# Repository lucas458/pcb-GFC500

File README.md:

# pcb-GFC500
Placa do Garmin GFC-500

### GFC-500 Real

### Placa Frontal

### Interface USB

### Placa Frontal e Interface USB

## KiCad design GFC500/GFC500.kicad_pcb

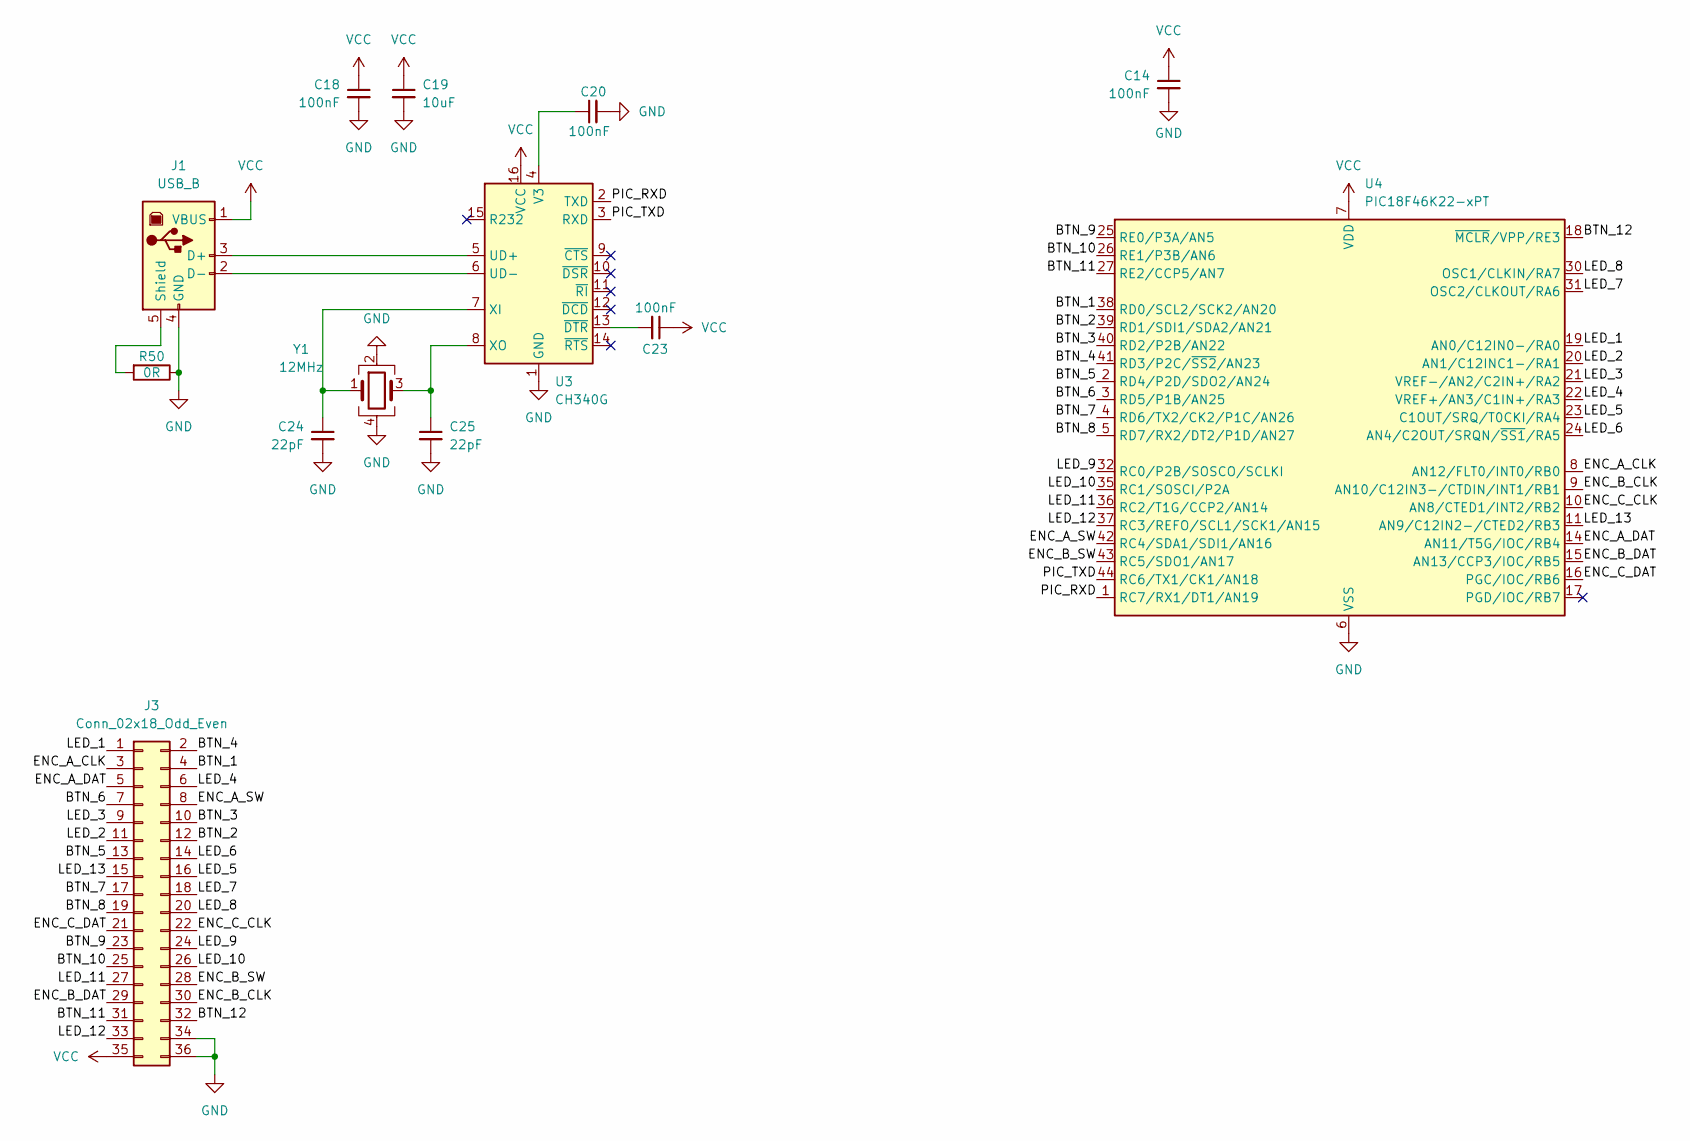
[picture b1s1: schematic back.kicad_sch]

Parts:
C14, C18, C20, C23: 100nF; C_0603_1608Metric
C19: 10uF; C_0805_2012Metric
C24, C25: 22pF; C_0603_1608Metric
J1: USB_B; A-USBSB
J3: Conn_02x18_Odd_Even; CONN36_901303436_MOL_H
R50: 0R; R_0603_1608Metric
U3: CH340G; SOIC-16_3.9x9.9mm_P1.27mm
U4: PIC18F46K22-xPT; TQFP-44_10x10mm_P0.8mm
Y1: 12MHz; Crystal_SMD_3225-4Pin_3.2x2.5mm

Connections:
/Back/BTN_1: J3.4, U4.38 (RD0/SCL2/SCK2/AN20)
/Back/BTN_2: J3.12, U4.39 (RD1/SDI1/SDA2/AN21)
/Back/BTN_3: J3.10, U4.40 (RD2/P2B/AN22)
/Back/BTN_4: J3.2, U4.41 (RD3/P2C/~SS2/AN23)
/Back/BTN_5: J3.13, U4.2 (RD4/P2D/SDO2/AN24)
/Back/BTN_6: J3.7, U4.3 (RD5/P1B/AN25)
/Back/BTN_7: J3.17, U4.4 (RD6/TX2/CK2/P1C/AN26)
/Back/BTN_8: J3.19, U4.5 (RD7/RX2/DT2/P1D/AN27)
/Back/BTN_9: J3.23, U4.25 (RE0/P3A/AN5)
/Back/BTN_10: J3.25, U4.26 (RE1/P3B/AN6)
/Back/BTN_11: J3.31, U4.27 (RE2/CCP5/AN7)
/Back/BTN_12: J3.32, U4.18 (~MCLR/VPP/RE3)
/Back/ENC_A_CLK: J3.3, U4.8 (AN12/FLT0/INT0/RB0)
/Back/ENC_A_DAT: J3.5, U4.14 (AN11/T5G/IOC/RB4)
/Back/ENC_A_SW: J3.8, U4.42 (RC4/SDA1/SDI1/AN16)
/Back/ENC_B_CLK: J3.30, U4.9 (AN10/C12IN3-/CTDIN/INT1/RB1)
/Back/ENC_B_DAT: J3.29, U4.15 (AN13/CCP3/IOC/RB5)
/Back/ENC_B_SW: J3.28, U4.43 (RC5/SDO1/AN17)
/Back/ENC_C_CLK: J3.22, U4.10 (AN8/CTED1/INT2/RB2)
/Back/ENC_C_DAT: J3.21, U4.16 (PGC/IOC/RB6)
/Back/LED_1: J3.1, U4.19 (AN0/C12IN0-/RA0)
/Back/LED_2: J3.11, U4.20 (AN1/C12INC1-/RA1)
/Back/LED_3: J3.9, U4.21 (VREF-/AN2/C2IN+/RA2)
/Back/LED_4: J3.6, U4.22 (VREF+/AN3/C1IN+/RA3)
/Back/LED_5: J3.16, U4.23 (C1OUT/SRQ/T0CKI/RA4)
/Back/LED_6: J3.14, U4.24 (AN4/C2OUT/SRQN/~SS1/RA5)
/Back/LED_7: J3.18, U4.31 (OSC2/CLKOUT/RA6)
/Back/LED_8: J3.20, U4.30 (OSC1/CLKIN/RA7)
/Back/LED_9: J3.24, U4.32 (RC0/P2B/SOSCO/SCLKI)
/Back/LED_10: J3.26, U4.35 (RC1/SOSCI/P2A)
/Back/LED_11: J3.27, U4.36 (RC2/T1G/CCP2/AN14)
/Back/LED_12: J3.33, U4.37 (RC3/REFO/SCL1/SCK1/AN15)
/Back/LED_13: J3.15, U4.11 (AN9/C12IN2-/CTED2/RB3)
/Back/PIC_RXD: U3.2 (TXD), U4.1 (RC7/RX1/DT1/AN19)
/Back/PIC_TXD: U3.3 (RXD), U4.44 (RC6/TX1/CK1/AN18)
GND: C14.2, C18.2, C19.2, C20.2, C24.2, C25.2, J1.4 (GND), J3.34, J3.36, R50.1, U3.1 (GND), U4.6 (VSS), U4.29 (VSS), Y1.2, Y1.4; also elsewhere on the board
unnamed: J1.3 (D+), U3.5 (UD+)
unnamed: J1.2 (D-), U3.6 (UD-)
unnamed: J1.5 (Shield), R50.2
unnamed: C20.1, U3.4 (V3)
unnamed: C24.1, U3.7 (XI), Y1.1
unnamed: C25.1, U3.8 (XO), Y1.3
unnamed: C23.2, U3.13 (~DTR)
VCC: C14.1, C18.1, C19.1, C23.1, J1.1 (VBUS), J3.35, U3.16 (VCC), U4.7 (VDD), U4.28 (VDD); also elsewhere on the board

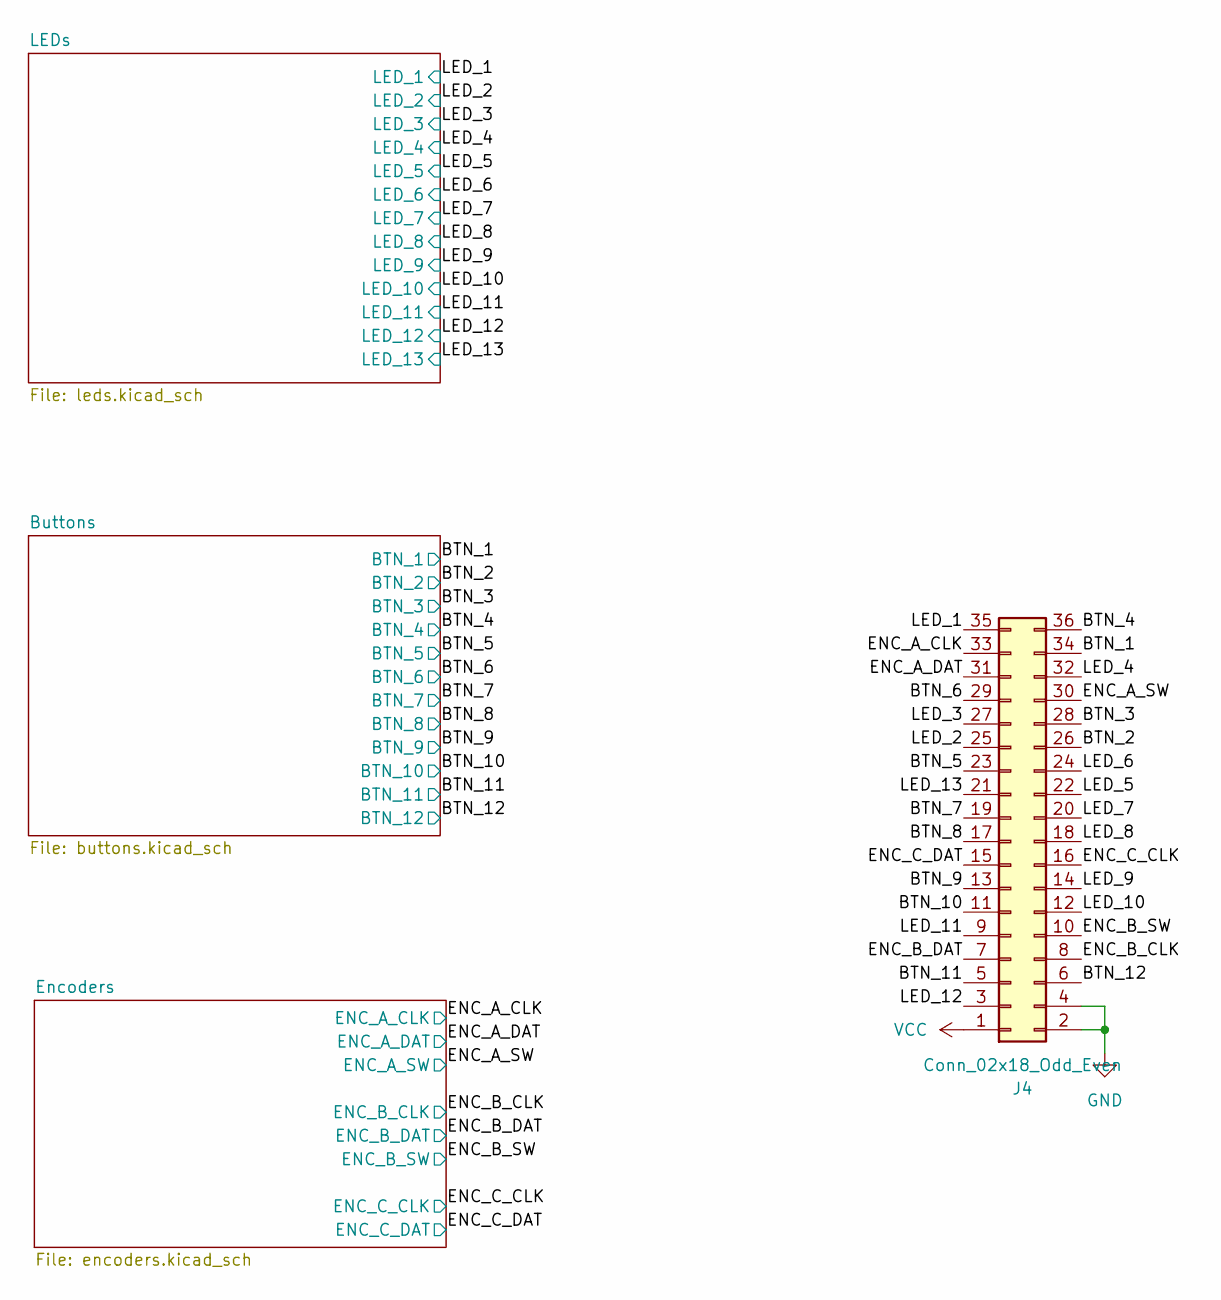
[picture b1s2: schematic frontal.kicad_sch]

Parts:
J4: Conn_02x18_Odd_Even; CONN36_901301436_MOL

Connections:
/Frontal/BTN_1: J4.34; also elsewhere on the board
/Frontal/BTN_2: J4.26; also elsewhere on the board
/Frontal/BTN_3: J4.28; also elsewhere on the board
/Frontal/BTN_4: J4.36; also elsewhere on the board
/Frontal/BTN_5: J4.23; also elsewhere on the board
/Frontal/BTN_6: J4.29; also elsewhere on the board
/Frontal/BTN_7: J4.19; also elsewhere on the board
/Frontal/BTN_8: J4.17; also elsewhere on the board
/Frontal/BTN_9: J4.13; also elsewhere on the board
/Frontal/BTN_10: J4.11; also elsewhere on the board
/Frontal/BTN_11: J4.5; also elsewhere on the board
/Frontal/BTN_12: J4.6; also elsewhere on the board
/Frontal/ENC_A_CLK: J4.33; also elsewhere on the board
/Frontal/ENC_A_DAT: J4.31; also elsewhere on the board
/Frontal/ENC_A_SW: J4.30; also elsewhere on the board
/Frontal/ENC_B_CLK: J4.8; also elsewhere on the board
/Frontal/ENC_B_DAT: J4.7; also elsewhere on the board
/Frontal/ENC_B_SW: J4.10; also elsewhere on the board
/Frontal/ENC_C_CLK: J4.16; also elsewhere on the board
/Frontal/ENC_C_DAT: J4.15; also elsewhere on the board
/Frontal/LED_1: J4.35; also elsewhere on the board
/Frontal/LED_2: J4.25; also elsewhere on the board
/Frontal/LED_3: J4.27; also elsewhere on the board
/Frontal/LED_4: J4.32; also elsewhere on the board
/Frontal/LED_5: J4.22; also elsewhere on the board
/Frontal/LED_6: J4.24; also elsewhere on the board
/Frontal/LED_7: J4.20; also elsewhere on the board
/Frontal/LED_8: J4.18; also elsewhere on the board
/Frontal/LED_9: J4.14; also elsewhere on the board
/Frontal/LED_10: J4.12; also elsewhere on the board
/Frontal/LED_11: J4.9; also elsewhere on the board
/Frontal/LED_12: J4.3; also elsewhere on the board
/Frontal/LED_13: J4.21; also elsewhere on the board
GND: J4.2, J4.4; also elsewhere on the board
VCC: J4.1; also elsewhere on the board

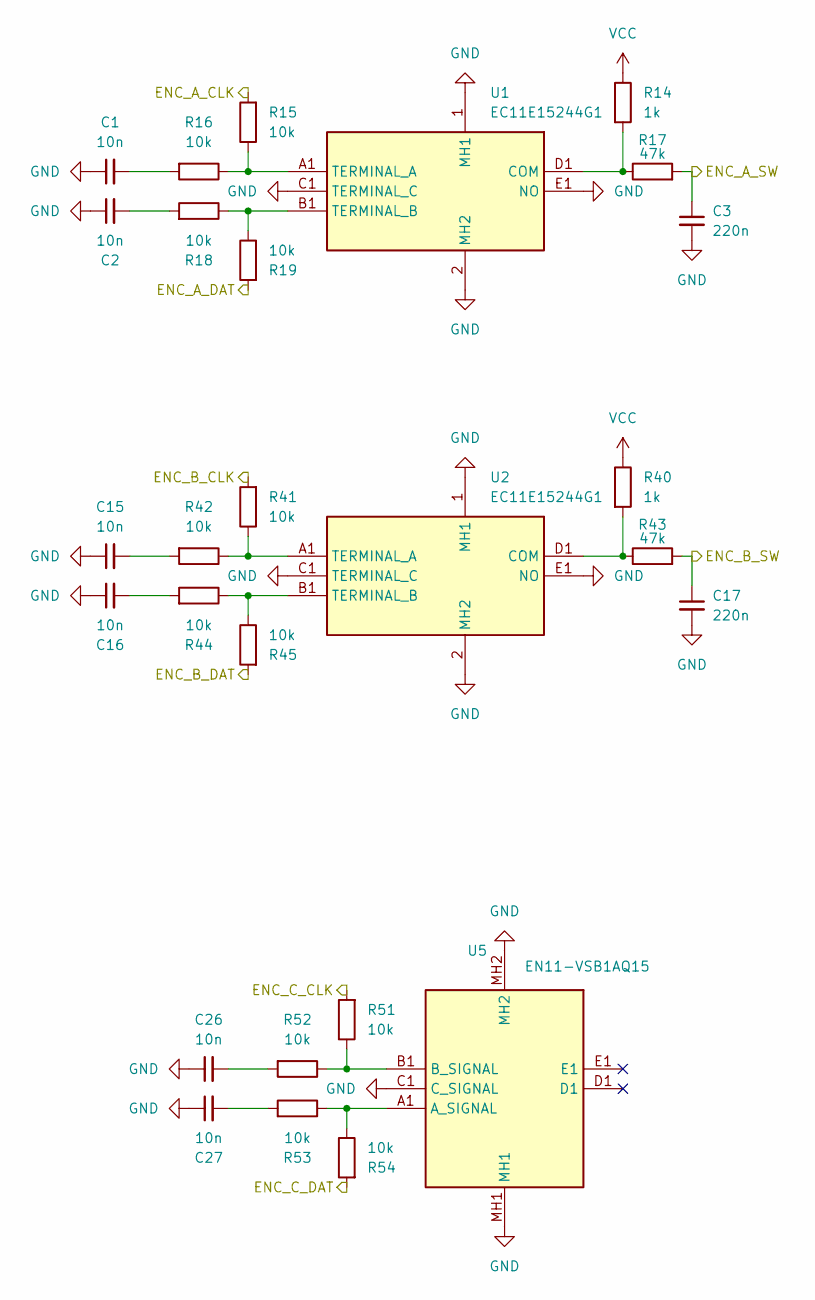
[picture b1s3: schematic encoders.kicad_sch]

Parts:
C1, C2, C15, C16, C26, C27: 10n; C_0603_1608Metric
C3, C17: 220n; C_0603_1608Metric
R14, R40: 1k; R_0603_1608Metric
R15, R16, R18, R19, R41, R42, R44, R45, R51, R52, R53, R54: 10k; R_0603_1608Metric
R17, R43: 47k; R_0603_1608Metric
U1, U2: EC11E15244G1; Manufacturer_Part_Number EC11E15244G1; Mouser Part Number 688-EC11E15244G1
U5: EN11-VSB1AQ15; EN11VSB1AQ15; Manufacturer_Part_Number EN11-VSB1AQ15; Mouser Part Number 858-EN11-VSB1AQ15

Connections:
/Frontal/ENC_A_CLK: R15.2; also elsewhere on the board
/Frontal/ENC_A_DAT: R19.2; also elsewhere on the board
/Frontal/ENC_A_SW: C3.1, R17.2; also elsewhere on the board
/Frontal/ENC_B_CLK: R41.2; also elsewhere on the board
/Frontal/ENC_B_DAT: R45.2; also elsewhere on the board
/Frontal/ENC_B_SW: C17.1, R43.2; also elsewhere on the board
/Frontal/ENC_C_CLK: R51.2; also elsewhere on the board
/Frontal/ENC_C_DAT: R54.2; also elsewhere on the board
GND: C1.1, C2.1, C3.2, C15.1, C16.1, C17.2, C26.1, C27.1, U1.1 (MH1), U1.2 (MH2), U1.C1 (TERMINAL_C), U1.E1 (NO), U2.1 (MH1), U2.2 (MH2), U2.C1 (TERMINAL_C), U2.E1 (NO), U5.C1 (C_SIGNAL), U5.MH1, U5.MH2; also elsewhere on the board
unnamed: C1.2, R16.2
unnamed: C2.2, R18.2
unnamed: C15.2, R42.2
unnamed: C16.2, R44.2
unnamed: C26.2, R52.2
unnamed: C27.2, R53.2
unnamed: R14.2, R17.1, U1.D1 (COM)
unnamed: R15.1, R16.1, U1.A1 (TERMINAL_A)
unnamed: R18.1, R19.1, U1.B1 (TERMINAL_B)
unnamed: R40.2, R43.1, U2.D1 (COM)
unnamed: R41.1, R42.1, U2.A1 (TERMINAL_A)
unnamed: R44.1, R45.1, U2.B1 (TERMINAL_B)
unnamed: R53.1, R54.1, U5.A1 (A_SIGNAL)
unnamed: R51.1, R52.1, U5.B1 (B_SIGNAL)
VCC: R14.1, R40.1; also elsewhere on the board

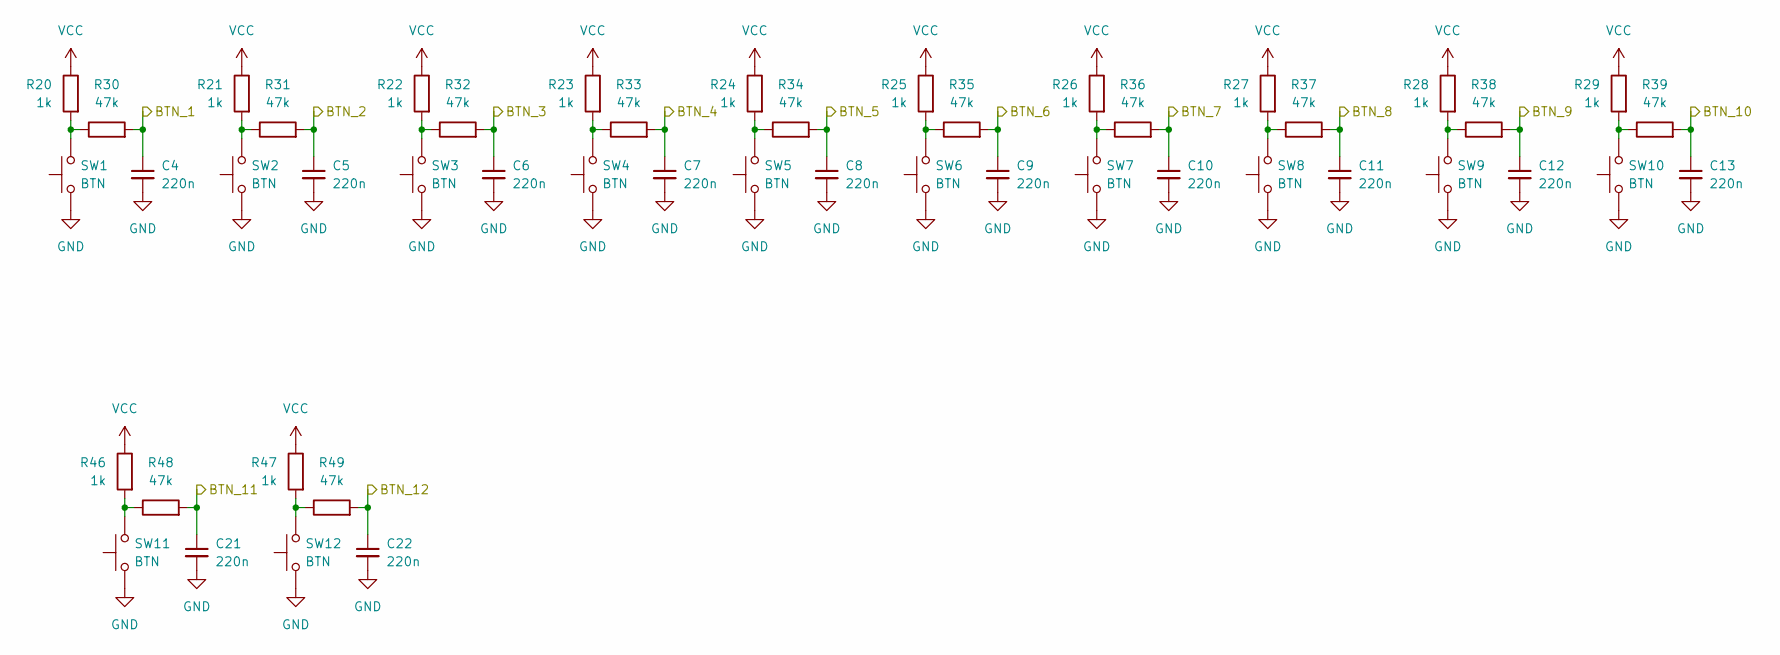
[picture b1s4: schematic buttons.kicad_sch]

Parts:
C4, C5, C6, C7, C8, C9, C10, C11, C12, C13, C21, C22: 220n; C_0603_1608Metric
R20, R21, R22, R23, R24, R25, R26, R27, R28, R29, R46, R47: 1k; R_0603_1608Metric
R30, R31, R32, R33, R34, R35, R36, R37, R38, R39, R48, R49: 47k; R_0603_1608Metric
SW1, SW2, SW3, SW4, SW5, SW6, SW7, SW8, SW9, SW10, SW11, SW12: BTN; SW_SPST_PTS647_Sx50

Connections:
/Frontal/BTN_1: C4.1, R30.2; also elsewhere on the board
/Frontal/BTN_2: C5.1, R31.2; also elsewhere on the board
/Frontal/BTN_3: C6.1, R32.2; also elsewhere on the board
/Frontal/BTN_4: C7.1, R33.2; also elsewhere on the board
/Frontal/BTN_5: C8.1, R34.2; also elsewhere on the board
/Frontal/BTN_6: C9.1, R35.2; also elsewhere on the board
/Frontal/BTN_7: C10.1, R36.2; also elsewhere on the board
/Frontal/BTN_8: C11.1, R37.2; also elsewhere on the board
/Frontal/BTN_9: C12.1, R38.2; also elsewhere on the board
/Frontal/BTN_10: C13.1, R39.2; also elsewhere on the board
/Frontal/BTN_11: C21.1, R48.2; also elsewhere on the board
/Frontal/BTN_12: C22.1, R49.2; also elsewhere on the board
GND: C4.2, C5.2, C6.2, C7.2, C8.2, C9.2, C10.2, C11.2, C12.2, C13.2, C21.2, C22.2, SW1.1, SW2.1, SW3.1, SW4.1, SW5.1, SW6.1, SW7.1, SW8.1, SW9.1, SW10.1, SW11.1, SW12.1; also elsewhere on the board
unnamed: R20.2, R30.1, SW1.2
unnamed: R21.2, R31.1, SW2.2
unnamed: R22.2, R32.1, SW3.2
unnamed: R23.2, R33.1, SW4.2
unnamed: R24.2, R34.1, SW5.2
unnamed: R25.2, R35.1, SW6.2
unnamed: R26.2, R36.1, SW7.2
unnamed: R27.2, R37.1, SW8.2
unnamed: R28.2, R38.1, SW9.2
unnamed: R29.2, R39.1, SW10.2
unnamed: R46.2, R48.1, SW11.2
unnamed: R47.2, R49.1, SW12.2
VCC: R20.1, R21.1, R22.1, R23.1, R24.1, R25.1, R26.1, R27.1, R28.1, R29.1, R46.1, R47.1; also elsewhere on the board

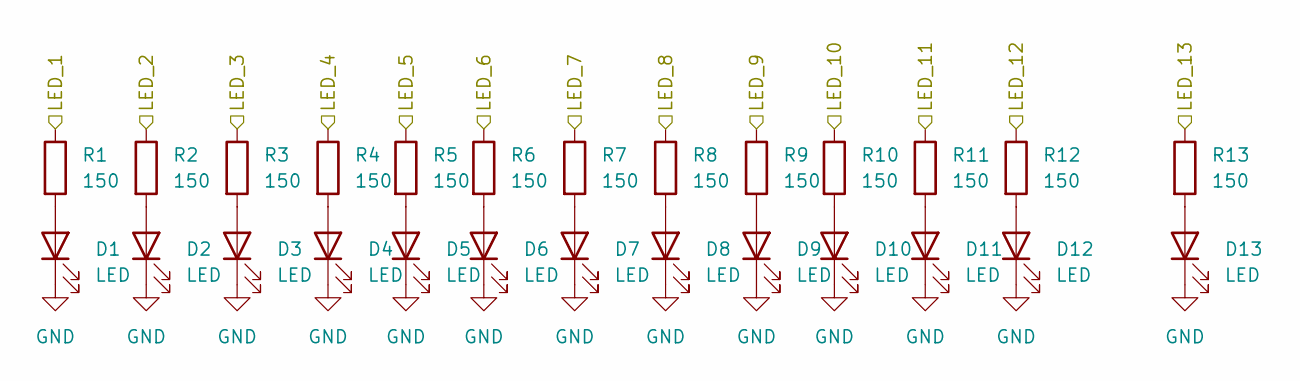
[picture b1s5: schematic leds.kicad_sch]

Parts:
D1, D2, D3, D4, D5, D6, D7, D8, D9, D10, D11, D12, D13: LED; LED_D3.0mm
R1, R2, R3, R4, R5, R6, R7, R8, R9, R10, R11, R12, R13: 150; R_0603_1608Metric

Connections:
/Frontal/LED_1: R1.1; also elsewhere on the board
/Frontal/LED_2: R2.1; also elsewhere on the board
/Frontal/LED_3: R3.1; also elsewhere on the board
/Frontal/LED_4: R4.1; also elsewhere on the board
/Frontal/LED_5: R5.1; also elsewhere on the board
/Frontal/LED_6: R6.1; also elsewhere on the board
/Frontal/LED_7: R7.1; also elsewhere on the board
/Frontal/LED_8: R8.1; also elsewhere on the board
/Frontal/LED_9: R9.1; also elsewhere on the board
/Frontal/LED_10: R10.1; also elsewhere on the board
/Frontal/LED_11: R11.1; also elsewhere on the board
/Frontal/LED_12: R12.1; also elsewhere on the board
/Frontal/LED_13: R13.1; also elsewhere on the board
GND: D1.1 (K), D2.1 (K), D3.1 (K), D4.1 (K), D5.1 (K), D6.1 (K), D7.1 (K), D8.1 (K), D9.1 (K), D10.1 (K), D11.1 (K), D12.1 (K), D13.1 (K); also elsewhere on the board
unnamed: D1.2 (A), R1.2
unnamed: D2.2 (A), R2.2
unnamed: D3.2 (A), R3.2
unnamed: D4.2 (A), R4.2
unnamed: D5.2 (A), R5.2
unnamed: D6.2 (A), R6.2
unnamed: D7.2 (A), R7.2
unnamed: D8.2 (A), R8.2
unnamed: D9.2 (A), R9.2
unnamed: D10.2 (A), R10.2
unnamed: D11.2 (A), R11.2
unnamed: D12.2 (A), R12.2
unnamed: D13.2 (A), R13.2

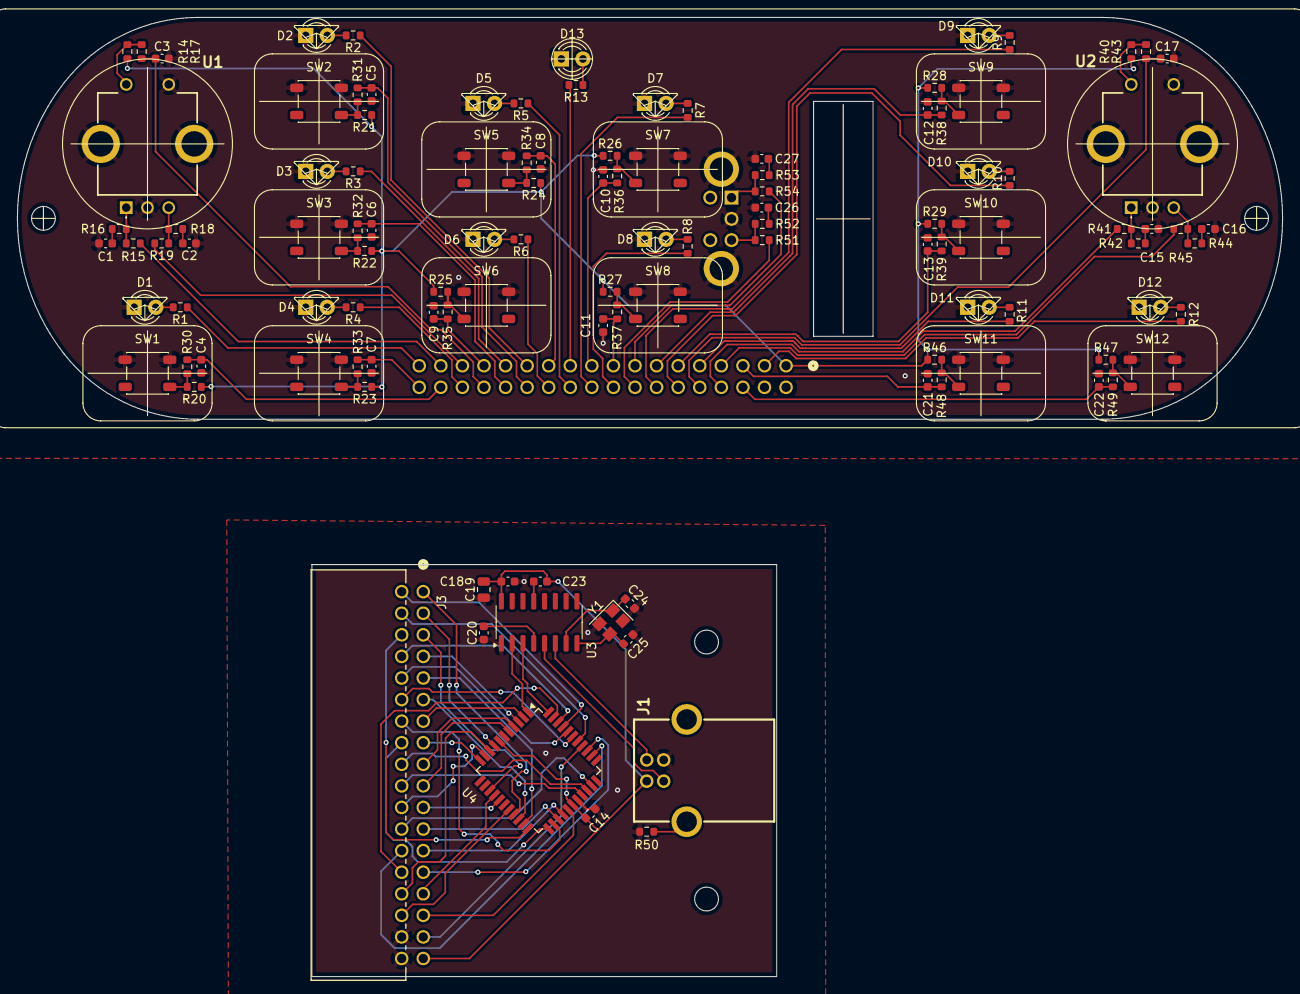
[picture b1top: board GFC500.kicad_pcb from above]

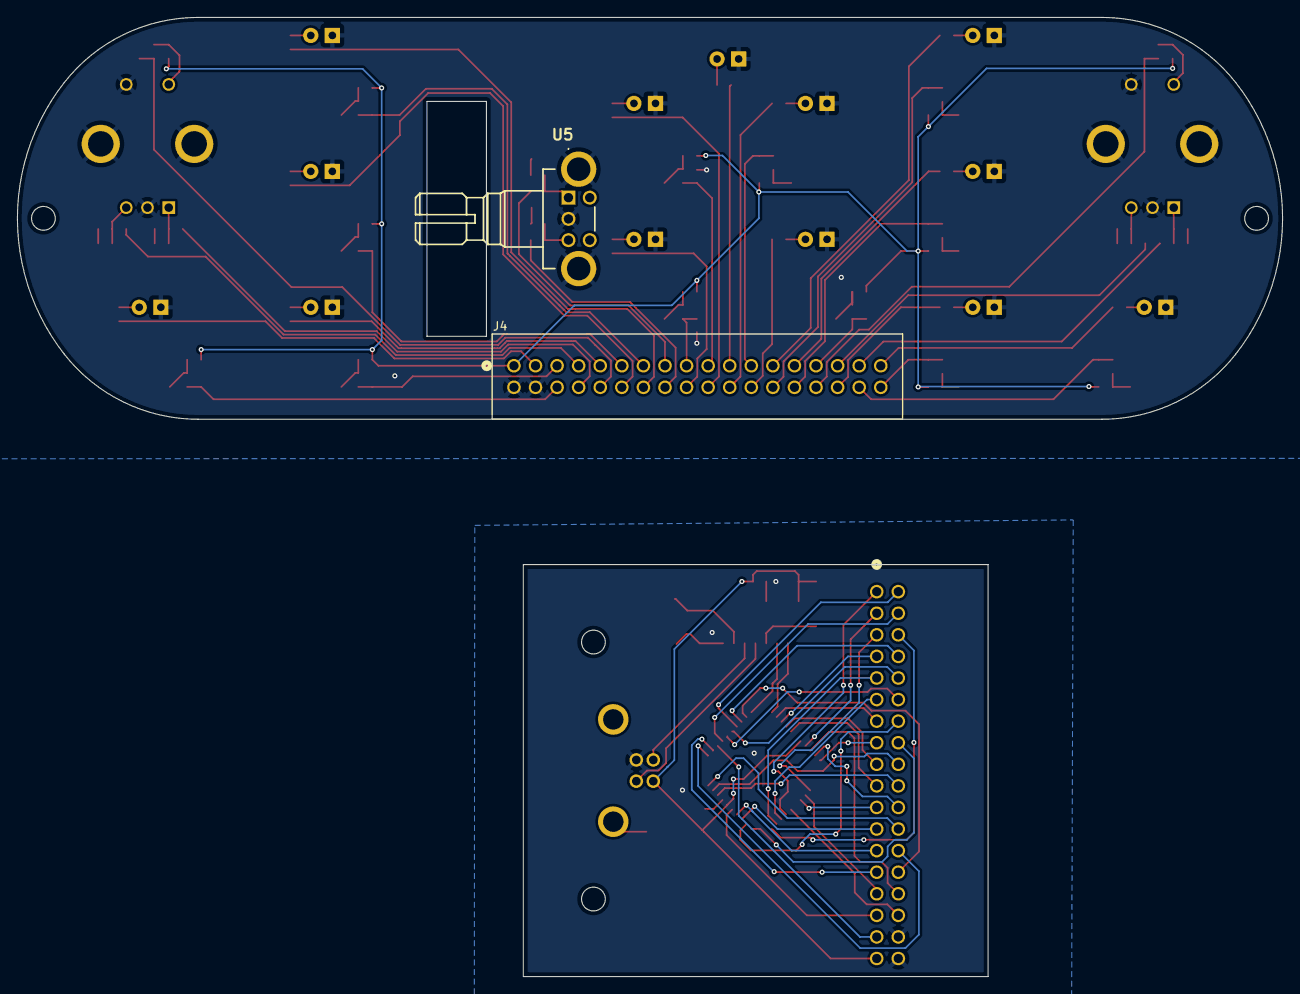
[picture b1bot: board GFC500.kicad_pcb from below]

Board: 2 copper layers, 148.9 x 47.3 mm, 115 parts (2 on the bottom side), 116 nets.

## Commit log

2025-10-24 chore: Commit inicial
2025-10-24 docs: Adicionado imagens ao README.md
2025-10-24 docs: Correção do path de imagem do GFC500 real
